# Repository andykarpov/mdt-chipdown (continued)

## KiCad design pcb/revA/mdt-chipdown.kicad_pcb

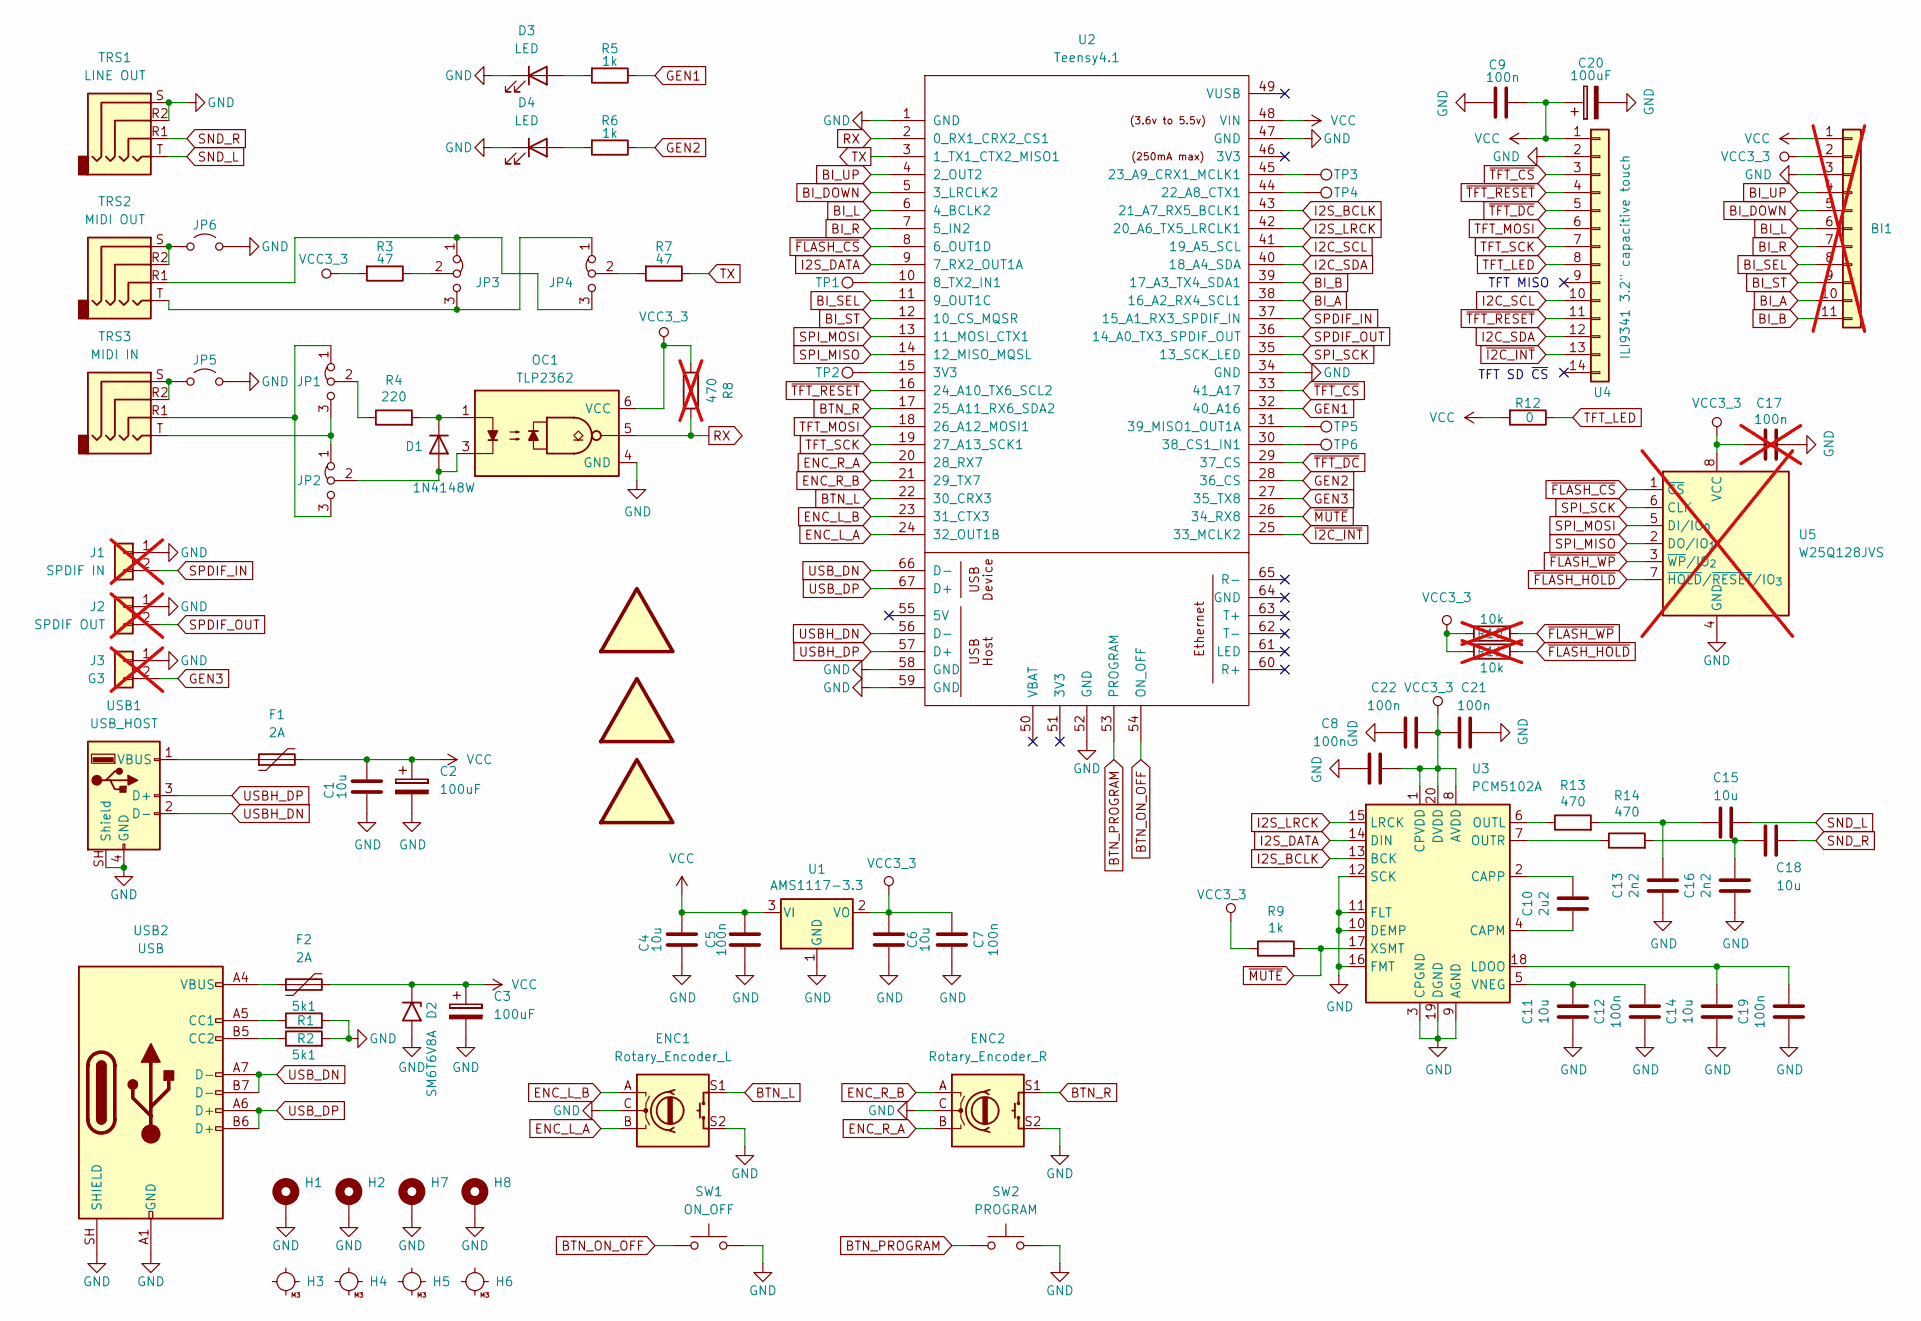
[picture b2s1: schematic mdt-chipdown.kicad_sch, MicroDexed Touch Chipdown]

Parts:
BI1: Conn_01x11; PinHeader_1x11_P2.54mm_Vertical; not fitted
C1, C4, C6, C11, C14, C15, C18: 10u; C_0805_2012Metric_Pad1.18x1.45mm_HandSolder
C2, C3, C20: 100uF; CP_EIA-6032-28_Kemet-C_HandSolder
C5, C7, C8, C9, C12, C19, C21, C22: 100n; C_0805_2012Metric_Pad1.18x1.45mm_HandSolder
C10: 2u2; C_0805_2012Metric_Pad1.18x1.45mm_HandSolder
C13, C16: 2n2; C_0805_2012Metric_Pad1.18x1.45mm_HandSolder
C17: 100n; C_0805_2012Metric_Pad1.18x1.45mm_HandSolder; not fitted
D1: 1N4148W; D_SOD-123
D2: SM6T6V8A; D_SMB_Handsoldering
D3, D4: LED; LED_Indicator_D3.0mm_W4.6mm_L6.5mm
ENC1: Rotary_Encoder_L; RotaryEncoder_Alps_EC11E-Switch_Vertical_H20mm
ENC2: Rotary_Encoder_R; RotaryEncoder_Alps_EC11E-Switch_Vertical_H20mm
F1, F2: 2A; Fuse_1812_4532Metric_Pad1.30x3.40mm_HandSolder
H1, H2, H7, H8: MountingHole_Pad; MountingHole_3mm_Pad_Via
H3, H4, H5, H6: MountingHole_M3
J1: SPDIF IN; Pin_Header_Straight_1x02; Part Number 1-0201FBV0T; not fitted
J2: SPDIF OUT; Pin_Header_Straight_1x02; Part Number 1-0201FBV0T; not fitted
J3: G3; Pin_Header_Straight_1x02; Part Number 1-0201FBV0T; not fitted
JP1, JP2, JP3, JP4: Jumper_3_Bridged12; SolderJumper-3_P1.3mm_Bridged12_RoundedPad1.0x1.5mm
JP5, JP6: Jumper_2_Open; SolderJumper-2_P1.3mm_Open_RoundedPad1.0x1.5mm
LOGO1: logo; andy_karpov_logo5_silk
LOGO2: logo; KiCad-Logo2_6mm_SilkScreen
LOGO3: logo; microDXD_logo12
OC1: TLP2362; SO-5_4.4x3.6mm_P1.27mm
R1, R2: 5k1; R_0805_2012Metric_Pad1.20x1.40mm_HandSolder
R3, R7: 47; R_0805_2012Metric_Pad1.20x1.40mm_HandSolder
R4: 220; R_0805_2012Metric_Pad1.20x1.40mm_HandSolder
R5, R6, R9: 1k; R_0805_2012Metric_Pad1.20x1.40mm_HandSolder
R8: 470; R_0805_2012Metric_Pad1.20x1.40mm_HandSolder; not fitted
R10, R11: 10k; R_0805_2012Metric_Pad1.20x1.40mm_HandSolder; not fitted
R12: 0; R_0805_2012Metric_Pad1.20x1.40mm_HandSolder
R13, R14: 470; R_0805_2012Metric_Pad1.20x1.40mm_HandSolder
SW1: ON_OFF; Push_PTH_RA_8-020_h7.5mm
SW2: PROGRAM; Push_PTH_RA_8-020_h7.5mm
TP1, TP2, TP3, TP4, TP5, TP6: TestPoint; TestPoint_Pad_2.0x2.0mm
TRS1: LINE OUT; AUDIO_JACK_3.5MM_SMD_TRRS_rounded_mixed
TRS2: MIDI OUT; AUDIO_JACK_3.5MM_SMD_TRRS_rounded_mixed
TRS3: MIDI IN; AUDIO_JACK_3.5MM_SMD_TRRS_rounded_mixed
U1: AMS1117-3.3; TO-252-2
U2: Teensy4.1; Teensy41
U3: PCM5102A; TSSOP-20_4.4x6.5mm_P0.65mm
U4: ILI9341 3.2" capacitive touch; PinSocket_1x14_P2.54mm_Vertical
U5: W25Q128JVS; SOIC-8_5.3x5.3mm_P1.27mm; not fitted
USB1: USB_HOST; USB_A_Molex_67643_Horizontal
USB2: USB; USB_C_Receptacle_G-Switch_GT-USB-7010ASV

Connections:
BI_A: BI1.10, U2.38 (16_A2_RX4_SCL1)
BI_B: BI1.11, U2.39 (17_A3_TX4_SDA1)
BI_DOWN: BI1.5, U2.5 (3_LRCLK2)
BI_L: BI1.6, U2.6 (4_BCLK2)
BI_R: BI1.7, U2.7 (5_IN2)
BI_SEL: BI1.8, U2.11 (9_OUT1C)
BI_ST: BI1.9, U2.12 (10_CS_MQSR)
BI_UP: BI1.4, U2.4 (2_OUT2)
BTN_L: ENC1.S1, U2.22 (30_CRX3)
BTN_ON_OFF: SW1.1, U2.54 (ON_OFF)
BTN_PROGRAM: SW2.1, U2.53 (PROGRAM)
BTN_R: ENC2.S1, U2.17 (25_A11_RX6_SDA2)
ENC_L_A: ENC1.B, U2.24 (32_OUT1B)
ENC_L_B: ENC1.A, U2.23 (31_CTX3)
ENC_R_A: ENC2.B, U2.20 (28_RX7)
ENC_R_B: ENC2.A, U2.21 (29_TX7)
GEN1: R5.1, U2.32 (40_A16)
GEN2: R6.1, U2.28 (36_CS)
GEN3: J3.2, U2.27 (35_TX8)
GND: BI1.3, C1.2, C2.2, C3.2, C4.2, C5.2, C6.2, C7.2, C8.2, C9.2, C11.1, C12.1, C13.1, C14.1, C16.1, C17.2, C19.1, C20.2, C21.1, C22.2, D2.2 (A2), D3.1 (K), D4.1 (K), ENC1.C, ENC1.S2, ENC2.C, ENC2.S2, H1.1 (1_1), H2.1 (1_1), H7.1 (1_1), H8.1 (1_1), J1.1, J2.1, J3.1, JP5.2 (B), JP6.2 (B), OC1.4 (GND), R1.2, R2.2, SW1.2, SW2.2, TRS1.R2, TRS1.S, U1.1 (GND), U2.1 (GND), U2.34 (GND), U2.47 (GND), U2.52 (GND), U2.58 (GND), U2.59 (GND), U3.3 (CPGND), U3.9 (AGND), U3.10 (DEMP), U3.11 (FLT), U3.12 (SCK), U3.16 (FMT), U3.19 (DGND), U4.2, U5.4 (GND), USB1.4 (GND), USB1.SH (Shield), USB2.A1 (GND), USB2.A12 (GND), USB2.B1 (GND), USB2.B12 (GND), USB2.SH (SHIELD)
I2C_SCL: U2.41 (19_A5_SCL), U4.10
I2C_SDA: U2.40 (18_A4_SDA), U4.12
I2S_BCLK: U2.43 (21_A7_RX5_BCLK1), U3.13 (BCK)
I2S_DATA: U2.9 (7_RX2_OUT1A), U3.14 (DIN)
I2S_LRCK: U2.42 (20_A6_TX5_LRCLK1), U3.15 (LRCK)
unnamed: C13.2, C15.2, R13.2
unnamed: C16.2, C18.2, R14.2
unnamed: D1.2 (A), JP2.2 (C), OC1.3
unnamed: D1.1 (K), OC1.1, R4.2
unnamed: D3.2 (A), R5.2
unnamed: D4.2 (A), R6.2
unnamed: F2.1, USB2.A4 (VBUS), USB2.A9 (VBUS), USB2.B4 (VBUS), USB2.B9 (VBUS)
unnamed: JP1.1 (A), JP2.3 (B), TRS3.R1
unnamed: JP1.3 (B), JP2.1 (A), TRS3.T
unnamed: JP1.2 (C), R4.1
unnamed: JP3.1 (A), JP4.3 (B), TRS2.R1
unnamed: JP3.3 (B), JP4.1 (A), TRS2.T
unnamed: JP3.2 (C), R3.1
unnamed: JP4.2 (C), R7.2
unnamed: JP5.1 (A), TRS3.R2, TRS3.S
unnamed: JP6.1 (A), TRS2.R2, TRS2.S
unnamed: TP2.1 (1_1), U2.15 (3V3)
unnamed: TP1.1 (1_1), U2.10 (8_TX2_IN1)
unnamed: TP4.1 (1_1), U2.44 (22_A8_CTX1)
unnamed: TP3.1 (1_1), U2.45 (23_A9_CRX1_MCLK1)
unnamed: TP6.1 (1_1), U2.30 (38_CS1_IN1)
unnamed: TP5.1 (1_1), U2.31 (39_MISO1_OUT1A)
unnamed: C10.1, U3.4 (CAPM)
unnamed: C10.2, U3.2 (CAPP)
unnamed: C14.2, C19.2, U3.18 (LDOO)
unnamed: R13.1, U3.6 (OUTL)
unnamed: R14.1, U3.7 (OUTR)
unnamed: C11.2, C12.2, U3.5 (VNEG)
unnamed: F1.1, USB1.1 (VBUS)
unnamed: R1.1, USB2.A5 (CC1)
unnamed: R2.1, USB2.B5 (CC2)
RX: OC1.5, R8.2, U2.2 (0_RX1_CRX2_CS1)
SND_L: C15.1, TRS1.T
SND_R: C18.1, TRS1.R1
SPDIF_IN: J1.2, U2.37 (15_A1_RX3_SPDIF_IN)
SPDIF_OUT: J2.2, U2.36 (14_A0_TX3_SPDIF_OUT)
SPI_MISO: U2.14 (12_MISO_MQSL), U5.2 (DO/IO_{1})
SPI_MOSI: U2.13 (11_MOSI_CTX1), U5.5 (DI/IO_{0})
SPI_SCK: U2.35 (13_SCK_LED), U5.6 (CLK)
TFT_LED: R12.1, U4.8
TFT_MOSI: U2.18 (26_A12_MOSI1), U4.6
TFT_SCK: U2.19 (27_A13_SCK1), U4.7
TX: R7.1, U2.3 (1_TX1_CTX2_MISO1)
USBH_DN: U2.56 (D-), USB1.2 (D-)
USBH_DP: U2.57 (D+), USB1.3 (D+)
USB_DN: U2.66 (D-), USB2.A7 (D-), USB2.B7 (D-)
USB_DP: U2.67 (D+), USB2.A6 (D+), USB2.B6 (D+)
VCC: BI1.1, C1.1, C2.1, C3.1, C4.1, C5.1, C9.1, C20.1, D2.1 (A1), F1.2, F2.2, R12.2, U1.3 (VI), U2.48 (VIN), U4.1
VCC3_3: BI1.2, C6.1, C7.1, C8.1, C17.1, C21.2, C22.1, OC1.6 (VCC), R3.2, R8.1, R9.1, R10.2, R11.2, U1.2 (VO), U3.1 (CPVDD), U3.8 (AVDD), U3.20 (DVDD), U5.8 (VCC)
~FLASH_CS: U2.8 (6_OUT1D), U5.1 (~CS)
~FLASH_HOLD: R11.1, U5.7 (~HOLD/~RESET/IO_{3})
~FLASH_WP: R10.1, U5.3 (~WP/IO_{2})
~I2C_INT: U2.25 (33_MCLK2), U4.13
~MUTE: R9.2, U2.26 (34_RX8), U3.17 (XSMT)
~TFT_CS: U2.33 (41_A17), U4.3
~TFT_DC: U2.29 (37_CS), U4.5
~TFT_RESET: U2.16 (24_A10_TX6_SCL2), U4.4, U4.11

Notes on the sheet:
TFT SD ~{CS}
TFT MISO

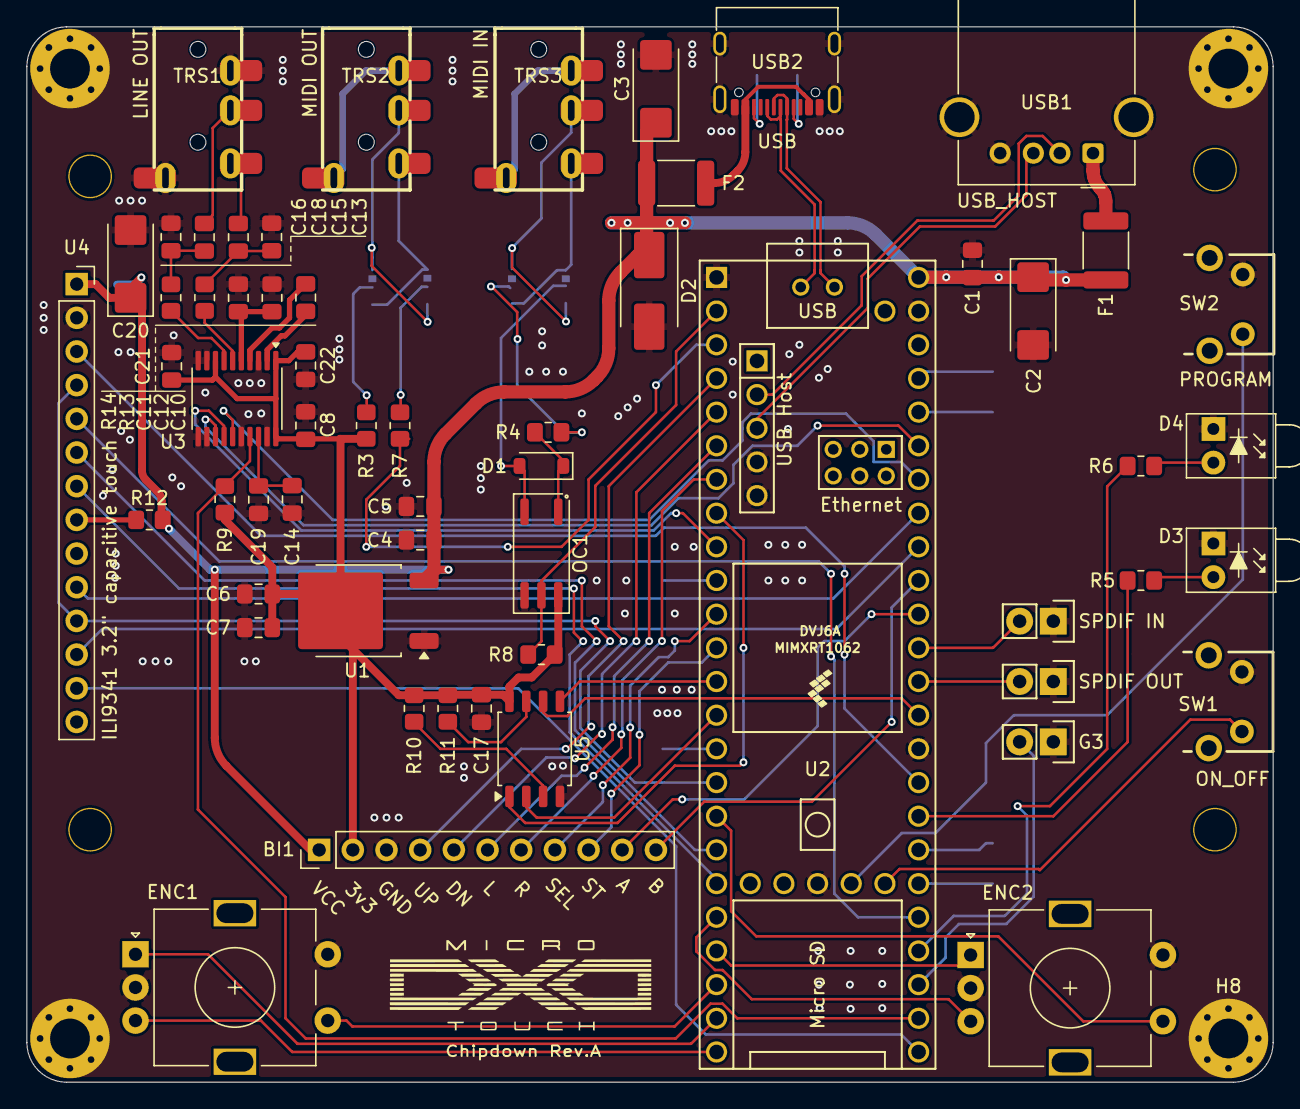
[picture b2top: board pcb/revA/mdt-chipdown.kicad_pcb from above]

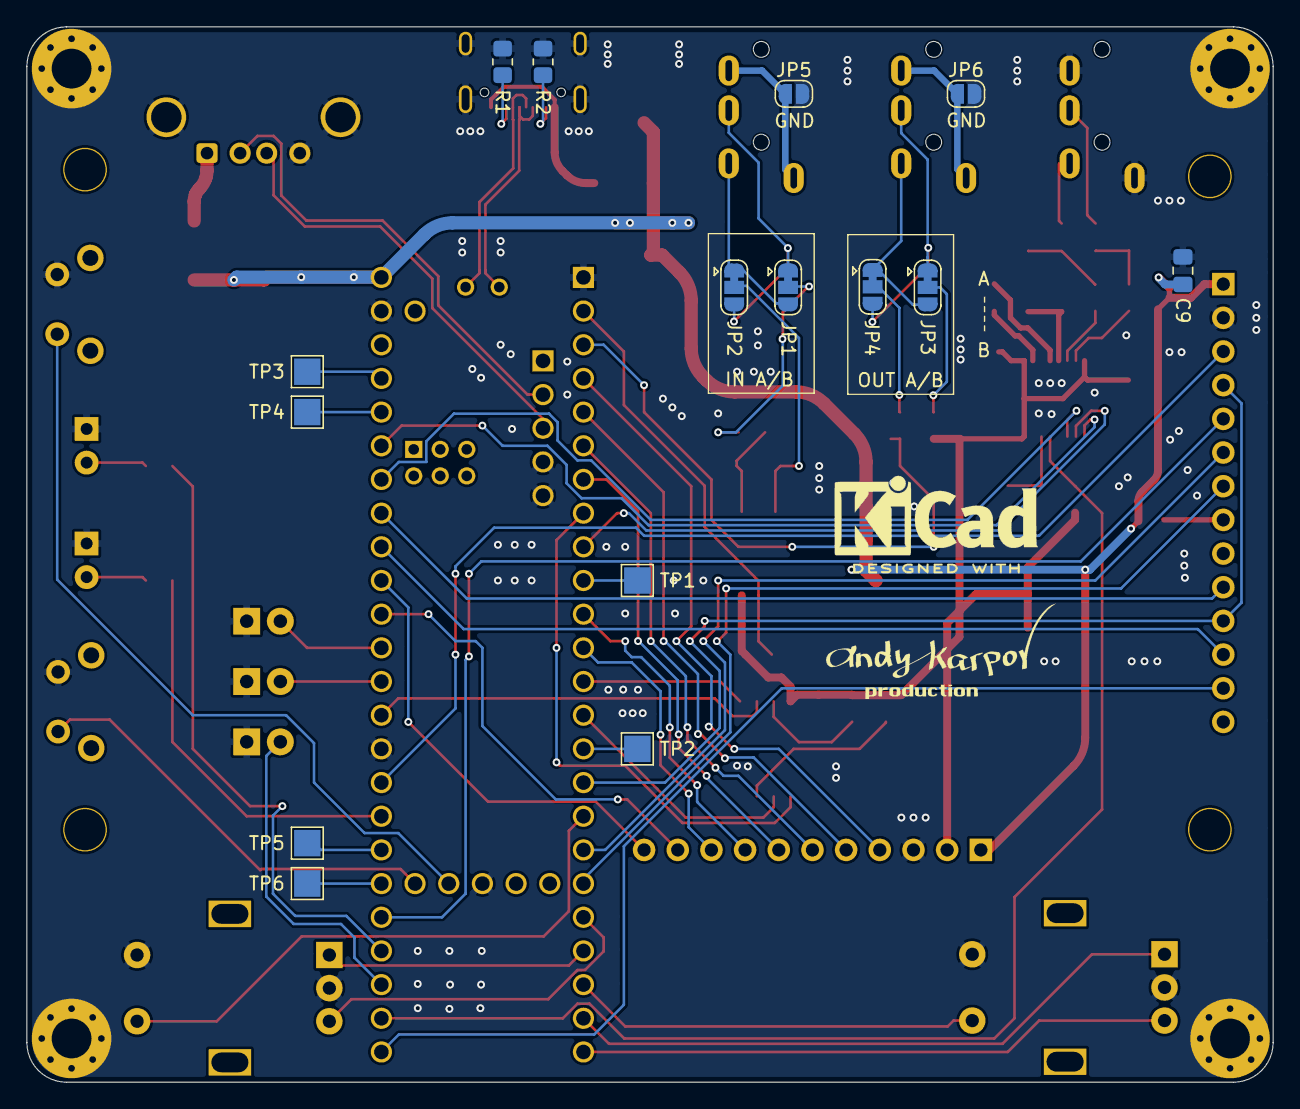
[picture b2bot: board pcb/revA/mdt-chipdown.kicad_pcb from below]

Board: 2 copper layers, 94.0 x 79.6 mm, 84 parts (17 on the bottom side), 82 nets.
